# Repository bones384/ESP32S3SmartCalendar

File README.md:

# E-Paper Smart Calendar
A low-power smart calendar device that displays upcoming events and weather information on an e-paper screen. Built around the ESP32-S3, the system is designed for long battery life, minimal power consumption, and reliable offline persistence.
Built around the ESP32-S3, the system is designed for long battery life, minimal power consumption, and reliable offline persistence.

## Features
- Google Calendar & weather integration: Fetches event data from the user's Google Calendar and weather forecast information from open-meteo.
  - Synced data is cached and saved to FRAM, avoiding the need to resync on every reboot, saving power.
- Ultra-low power system with aggressive power gating: The entire system is power gated using a P-MOSFET and a TPL5110, waking periodically to update the display.
  - Network sync is expensive in terms of power, and as such only happens every few automatic wakes.
  - WiFi remains disabled outside of sync cycles.
  - E-paper display retains the image without power
  - Powered by 4xAA batteries (designed for NiMH),
  - Will display warning and reduce power usage to minimum if voltage goes under a safe threshold.
> [!NOTE]
> These power saving techniques reduce the idle power usage to under a microampere, with short bursts of power consumption during a wake cycle.
> This increases battery life significantly.
- Interactive mode: The user can wake the device and browse events/forecasts for upcoming days.
- ESP SoftAP WiFi Provisioning: Network credentials can be configured from a mobile device using Espressif’s provisioning tools.
- Google API tokens are provisioned via serial connection and automatically refreshed when expired.
- Displays indoor temperature and humidity using onboard sensors.

## Key Components

* ESP32-S3 DevkitC-1
* Adafruit SHT40 breakout board (ADAFRUIT4885)
* 4MBit FRAM IC: MB85RS4MTPF-G-BCERE1, with a matching DIP adapter
* Pololu 3.3V step-down voltage regulator module DT24V10F3
* Waveshare 13353 4.2 inch E-Paper module
* TPL5110 Low Power Timer (with matching DIP adapter)
  
A full BOM can be found in the project report in the docs directory.

## Media

High-level system diagram:

Software flow diagram:

## Notes
Includes full schematic (.sch) and PCB layout (.brd) files.
Designed as a custom PCB and manufactured via JLCPCB.
All components were hand-soldered and the device was fully assembled and tested.
The /docs directory contains a detailed report with the BOM, assembly guide, and operating instructions.

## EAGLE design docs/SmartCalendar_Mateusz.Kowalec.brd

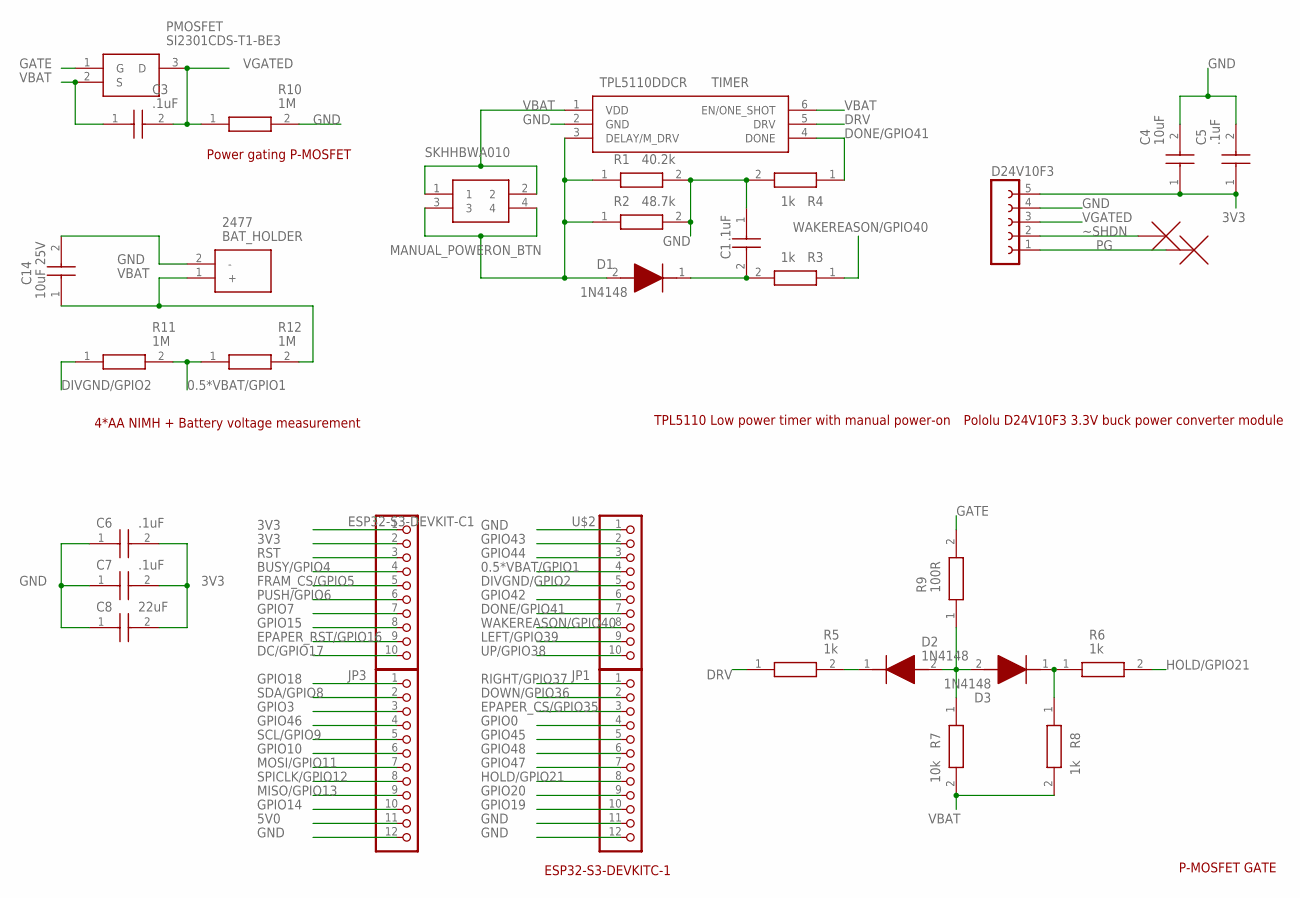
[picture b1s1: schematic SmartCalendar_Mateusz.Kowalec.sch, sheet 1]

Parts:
BAT_HOLDER: 2477
C1, C3, C5, C6, C7: .1uF; CAPC2012X94N
C4: 10uF; CAPC2012X140N
C8: 22uF; GRM31X
C14: 10uF 25V; GCM21
D1, D2, D3: 1N4148; DIOAD1150W50L390D190
D24V10F3: FE05-1
ESP32-S3-DEVKIT-C1: PINHD-1X10; 1X10-BIG
JP1, JP3: PINHD-1X12-CB; 1X12-CB
MANUAL_POWERON_BTN: SKHHBWA010; SKHHALA010
PMOSFET: SI2301CDS-T1-BE3; SOT95P237X112-3N
R1: 40.2k; RESC2012X60N
R2: 48.7k; RESC2012X60N
R3, R4, R5, R6, R8: 1k; RESC2012X50N
R7: 10k; RESC2012X60N
R9: 100R; RESC2012X50N
R10, R11, R12: 1M; RESC2012X62N
TIMER: TPL5110DDCR; SOT95P280X110-6N
U$2: PINHD-1X10; 1X10-BIG

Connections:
0.5*VBAT/GPIO1: R11.2, R12.1, U$2.4
3V3: C4.1, C5.1, C6.2, C7.2, C8.2, D24V10F3.5, ESP32-S3-DEVKIT-C1.1, ESP32-S3-DEVKIT-C1.2; also elsewhere on the board
5V0: JP3.11
BUSY/GPIO4: ESP32-S3-DEVKIT-C1.4; also elsewhere on the board
DC/GPIO17: ESP32-S3-DEVKIT-C1.10; also elsewhere on the board
DIVGND/GPIO2: R11.1, U$2.5
DONE/GPIO41: R4.1, TIMER.4 (DONE), U$2.7
DOWN/GPIO36: JP1.2; also elsewhere on the board
DRV: R5.1, TIMER.5 (DRV)
EPAPER_CS/GPIO35: JP1.3; also elsewhere on the board
EPAPER_RST/GPIO16: ESP32-S3-DEVKIT-C1.9; also elsewhere on the board
FRAM_CS/GPIO5: ESP32-S3-DEVKIT-C1.5; also elsewhere on the board
G: D2.2 (A), D3.2 (A), R7.1, R9.1
GATE: PMOSFET.1 (G), R9.2
GND: BAT_HOLDER.2 (-), C1.1, C4.2, C5.2, C6.1, C7.1, C8.1, C14.2, D24V10F3.4, JP1.11, JP1.12, JP3.12, R1.2, R2.2, R4.2, R10.2, TIMER.2 (GND), U$2.1; also elsewhere on the board
GPIO0: JP1.4
GPIO3: JP3.3
GPIO7: ESP32-S3-DEVKIT-C1.7
GPIO10: JP3.6
GPIO14: JP3.10
GPIO15: ESP32-S3-DEVKIT-C1.8
GPIO18: JP3.1
GPIO19: JP1.10
GPIO20: JP1.9
GPIO42: U$2.6
GPIO43: U$2.2
GPIO44: U$2.3
GPIO45: JP1.5
GPIO46: JP3.4
GPIO47: JP1.7
GPIO48: JP1.6
HOLD/GPIO21: JP1.8, R6.2
LEFT/GPIO39: U$2.9; also elsewhere on the board
MAN_REXT: D1.2 (A), MANUAL_POWERON_BTN.3, MANUAL_POWERON_BTN.4, R1.1, R2.1, TIMER.3 (DELAY/M_DRV)
MISO/GPIO13: JP3.9; also elsewhere on the board
MOSI/GPIO11: JP3.7; also elsewhere on the board
N: D2.1 (K), R5.2
unnamed: C1.2, D1.1 (K), R3.2
unnamed: D3.1 (K), R6.1, R8.1
PG: D24V10F3.1
PUSH/GPIO6: ESP32-S3-DEVKIT-C1.6; also elsewhere on the board
RIGHT/GPIO37: JP1.1; also elsewhere on the board
RST: ESP32-S3-DEVKIT-C1.3
SCL/GPIO9: JP3.5; also elsewhere on the board
SDA/GPIO8: JP3.2; also elsewhere on the board
SPICLK/GPIO12: JP3.8; also elsewhere on the board
UP/GPIO38: U$2.10; also elsewhere on the board
VBAT: BAT_HOLDER.1 (+), C3.1, C14.1, MANUAL_POWERON_BTN.1, MANUAL_POWERON_BTN.2, PMOSFET.2 (S), R7.2, R8.2, R12.2, TIMER.1 (VDD), TIMER.6 (EN/ONE_SHOT)
VGATED: C3.2, D24V10F3.3, PMOSFET.3 (D), R10.1
WAKEREASON/GPIO40: R3.1, U$2.8
~SHDN: D24V10F3.2

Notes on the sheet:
ESP32-S3-DEVKITC-1
4*AA NIMH + Battery voltage measurement
Power gating P-MOSFET
P-MOSFET GATE
TPL5110 Low power timer with manual power-on
Pololu D24V10F3 3.3V buck power converter module

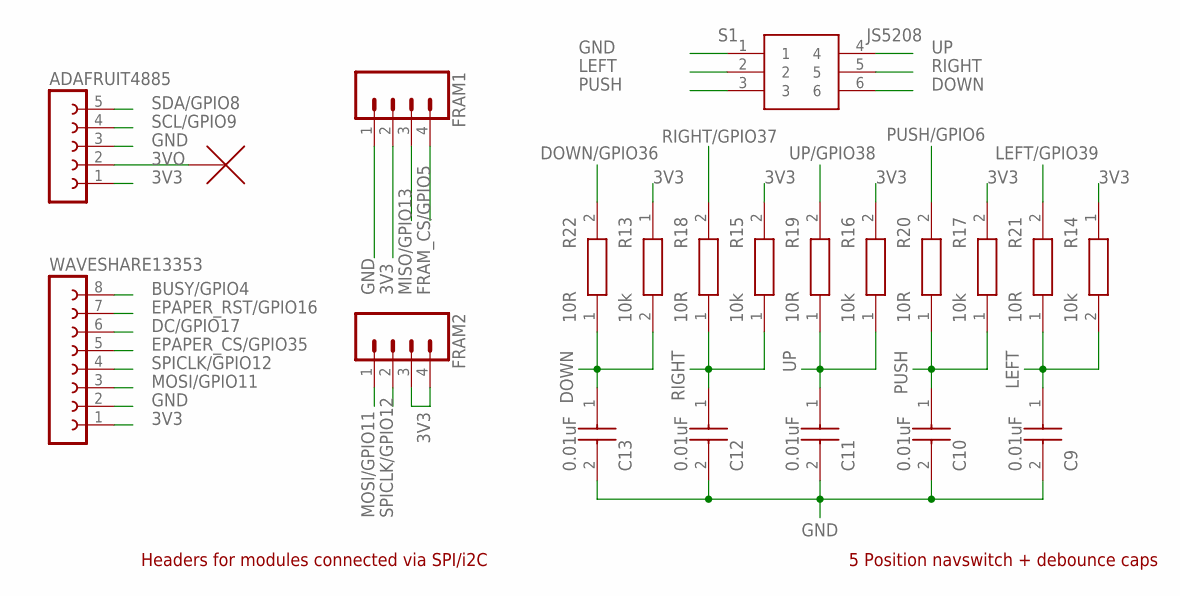
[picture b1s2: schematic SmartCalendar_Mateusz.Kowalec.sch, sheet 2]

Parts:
ADAFRUIT4885: FE05-1
C9, C10, C11, C12, C13: 0.01uF; CAPC2012X94N
FRAM1, FRAM2: CONN_04PTH; 1X04
R13, R14, R15, R16, R17: 10k; RESC2012X60N
R18, R19, R20, R21, R22: 10R; RESC2012X50N
S1: JS5208
WAVESHARE13353: FE08-1; FE08

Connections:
3V3: ADAFRUIT4885.1, FRAM1.2, FRAM2.3, FRAM2.4, R13.1, R14.1, R15.2, R16.2, R17.2, WAVESHARE13353.1; also elsewhere on the board
3VO: ADAFRUIT4885.2
BUSY/GPIO4: WAVESHARE13353.8; also elsewhere on the board
DC/GPIO17: WAVESHARE13353.6; also elsewhere on the board
DOWN: C13.1 (C1), R13.2, R22.1, S1.6
DOWN/GPIO36: R22.2; also elsewhere on the board
EPAPER_CS/GPIO35: WAVESHARE13353.5; also elsewhere on the board
EPAPER_RST/GPIO16: WAVESHARE13353.7; also elsewhere on the board
FRAM_CS/GPIO5: FRAM1.4; also elsewhere on the board
GND: ADAFRUIT4885.3, C9.2 (C2), C10.2 (C2), C11.2 (C2), C12.2 (C2), C13.2 (C2), FRAM1.1, S1.1, WAVESHARE13353.2; also elsewhere on the board
LEFT: C9.1 (C1), R14.2, R21.1, S1.2
LEFT/GPIO39: R21.2; also elsewhere on the board
MISO/GPIO13: FRAM1.3; also elsewhere on the board
MOSI/GPIO11: FRAM2.1, WAVESHARE13353.3; also elsewhere on the board
PUSH: C10.1 (C1), R17.1, R20.1, S1.3
PUSH/GPIO6: R20.2; also elsewhere on the board
RIGHT: C12.1 (C1), R15.1, R18.1, S1.5
RIGHT/GPIO37: R18.2; also elsewhere on the board
SCL/GPIO9: ADAFRUIT4885.4; also elsewhere on the board
SDA/GPIO8: ADAFRUIT4885.5; also elsewhere on the board
SPICLK/GPIO12: FRAM2.2, WAVESHARE13353.4; also elsewhere on the board
UP: C11.1 (C1), R16.1, R19.1, S1.4
UP/GPIO38: R19.2; also elsewhere on the board

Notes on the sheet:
5 Position navswitch + debounce caps
Headers for modules connected via SPI/i2C

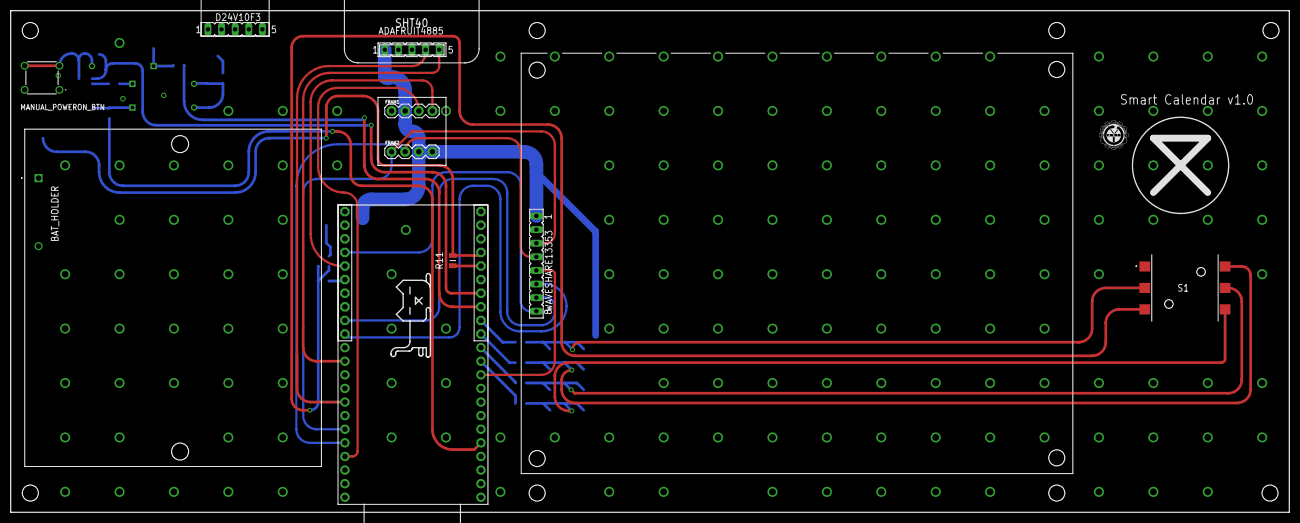
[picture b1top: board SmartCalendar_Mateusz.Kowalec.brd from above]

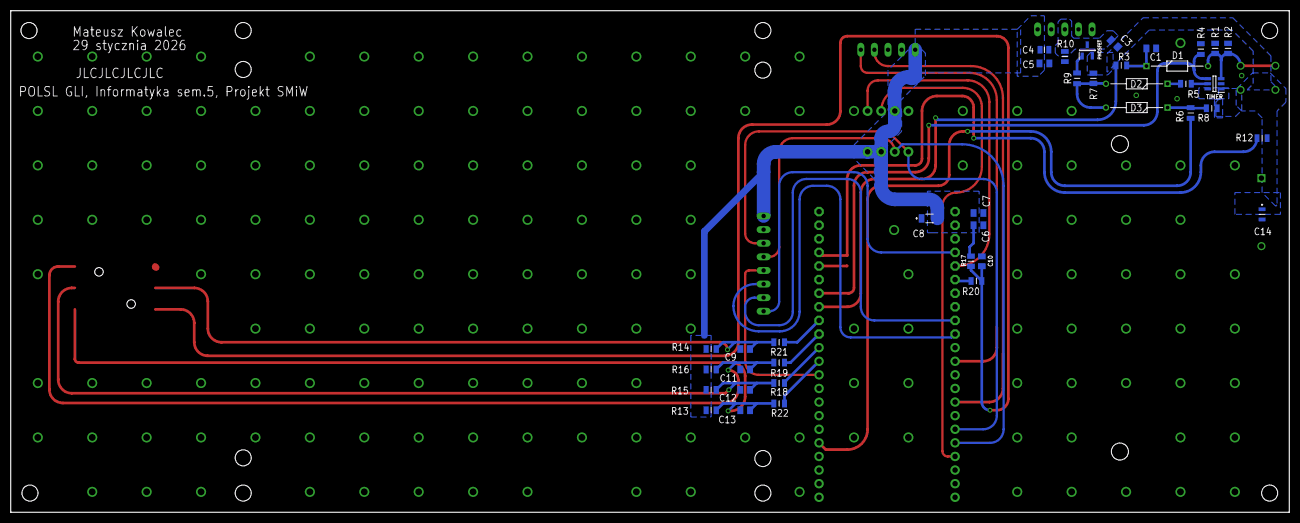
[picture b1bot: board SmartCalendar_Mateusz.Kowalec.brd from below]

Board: 2 copper layers, 238.7 x 93.7 mm, 52 parts (39 on the bottom side), 36 nets.

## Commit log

2026-01-31 Project created and pushed to github
2026-04-17 Work towards getting HTTPS responses from Google
2026-04-17 Testing stack usage
2026-04-17 Google API calendar event retrieval implemented.
2026-04-17 Testing weather api
2026-04-17 File structure changes
2026-04-17 All the basic network sync features implemented.
2026-04-17 Date compare operator fixed
2026-04-17 Network sync & data retrieval OK, moving on to automatic boot logic stuff
2026-04-17 Automatic boot skeleton
2026-04-17 Fetched data aggregation initial test
2026-04-17 Added GUI
2026-04-17 Added README.md
2026-04-17 Finalised GUI
2026-04-17 Added docs
2026-04-24 Reupload media
